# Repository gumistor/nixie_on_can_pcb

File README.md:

# nixie_on_can_pcb
Six NIXIE display with CAN bus interface. Powered with step up regulator.

Main controler: PIC18F2480
CAN transciever: MCP2551

PIC utylize PWM output to drive step-up regulator. 
Step-up regulator provides high voltage to lamps (over 100V!!). 
PIC uses multiplexing to light up digits.

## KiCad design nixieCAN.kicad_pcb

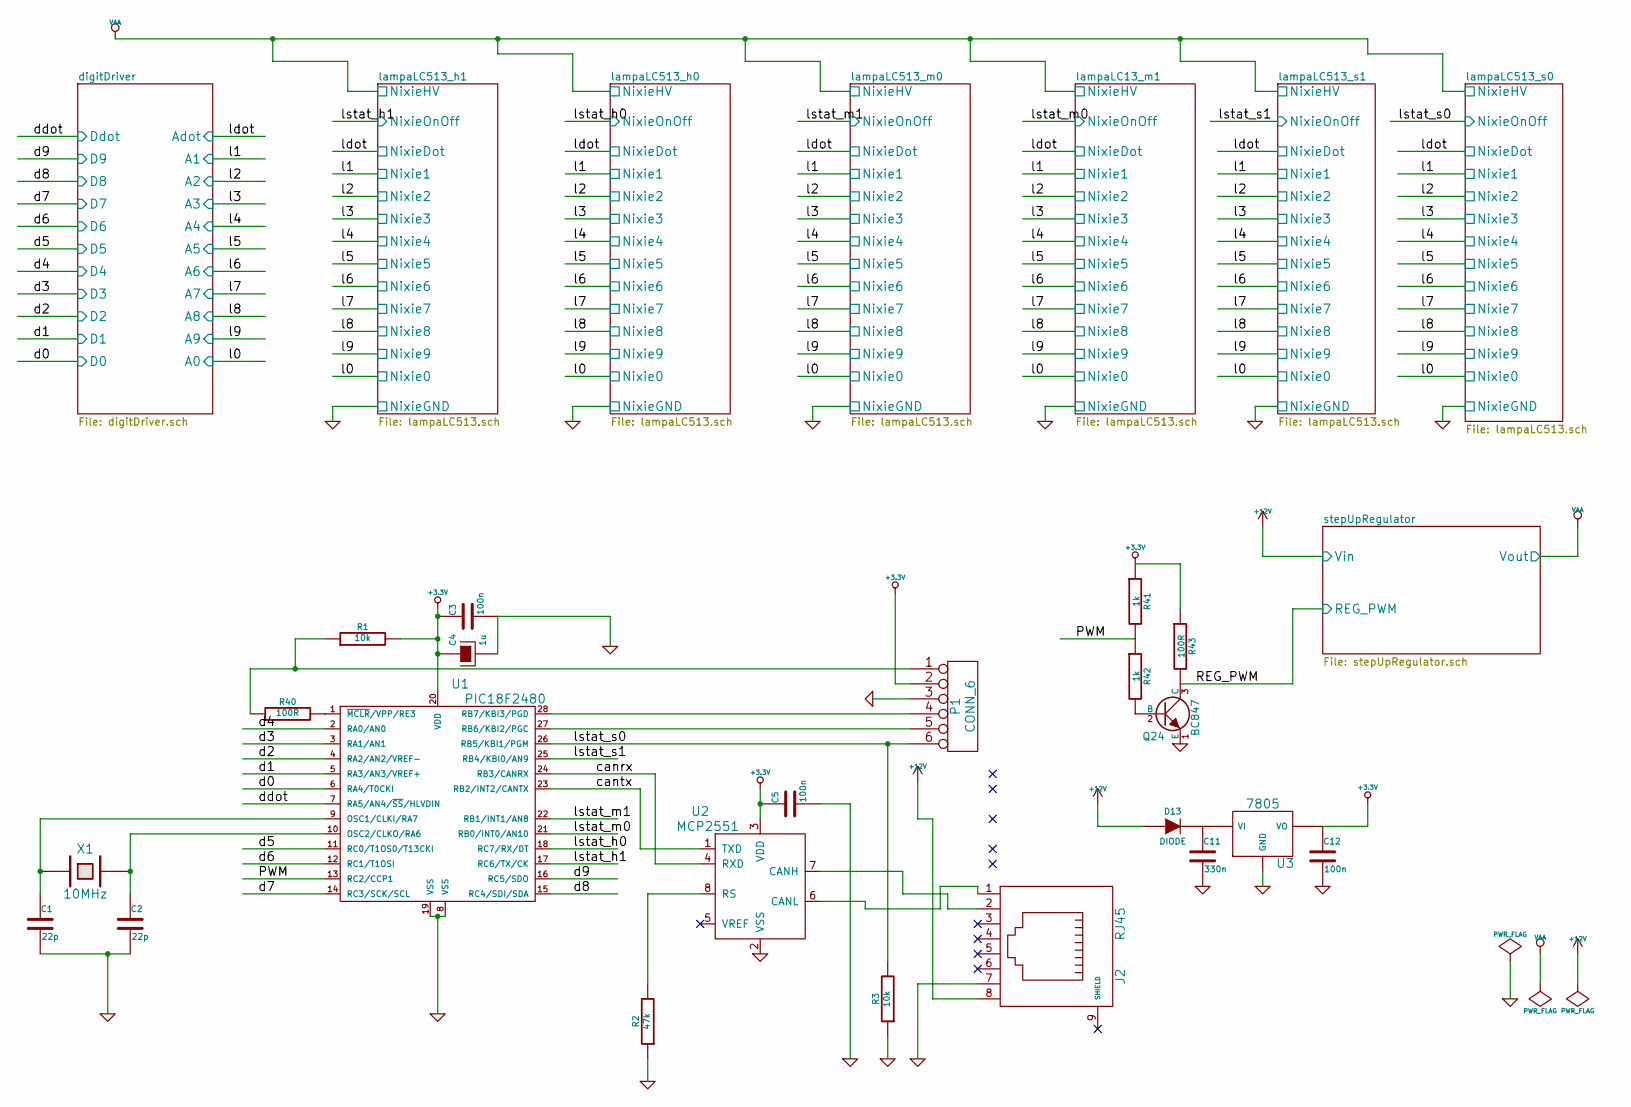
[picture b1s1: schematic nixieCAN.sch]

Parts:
C1, C2: 22p
C3, C5, C12: 100n
C4: 1u
C11: 330n
D13: DIODE
J2: RJ45
P1: CONN_6
Q24: BC847
R1, R3: 10k
R2: 47k
R40, R43: 100R
R41, R42: 1k
U1: PIC18F2480
U2: MCP2551
U3: 7805
X1: 10MHz

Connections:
+3.3V: C3.1, C4.1, C5.1, C12.1, P1.2, R1.2, R41.1, R43.1, U1.20 (VDD), U2.3 (VDD), U3.3 (VO)
+12V: D13.1 (A), J2.8; also elsewhere on the board
/PWM: R41.2, R42.1, U1.13 (RC2/CCP1)
/canrx: U1.24 (RB3/CANRX), U2.4 (RXD)
/cantx: U1.23 (RB2/INT2/CANTX), U2.1 (TXD)
/digitDriver/D0: U1.6 (RA4/T0CKI); also elsewhere on the board
/digitDriver/D1: U1.5 (RA3/AN3/VREF+); also elsewhere on the board
/digitDriver/D2: U1.4 (RA2/AN2/VREF-); also elsewhere on the board
/digitDriver/D3: U1.3 (RA1/AN1); also elsewhere on the board
/digitDriver/D4: U1.2 (RA0/AN0); also elsewhere on the board
/digitDriver/D5: U1.11 (RC0/T1OS0/T13CKI); also elsewhere on the board
/digitDriver/D6: U1.12 (RC1/T1OSI); also elsewhere on the board
/digitDriver/D7: U1.14 (RC3/SCK/SCL); also elsewhere on the board
/digitDriver/D8: U1.15 (RC4/SDI/SDA); also elsewhere on the board
/digitDriver/D9: U1.16 (RC5/SDO); also elsewhere on the board
/digitDriver/Ddot: U1.7 (RA5/AN4/~SS~/HLVDIN); also elsewhere on the board
/lampaLC13_m1/NixieOnOff: U1.21 (RB0/INT0/AN10); also elsewhere on the board
/lampaLC513_h0/NixieOnOff: U1.18 (RC7/RX/DT); also elsewhere on the board
/lampaLC513_h1/NixieOnOff: U1.17 (RC6/TX/CK); also elsewhere on the board
/lampaLC513_m0/NixieOnOff: U1.22 (RB1/INT1/AN8); also elsewhere on the board
/lampaLC513_s0/NixieOnOff: P1.6, R3.2, U1.26 (RB5/KBI1/PGM); also elsewhere on the board
/lampaLC513_s1/NixieOnOff: U1.25 (RB4/KBI0/AN9); also elsewhere on the board
/stepUpRegulator/REG_PWM: Q24.3 (C), R43.2; also elsewhere on the board
GND: C1.2, C2.2, C3.2, C4.2, C5.2, C11.2, C12.2, J2.7, P1.3, Q24.1 (E), R2.1, R3.1, U1.8 (VSS), U1.19 (VSS), U2.2 (VSS), U3.2 (GND); also elsewhere on the board
unnamed: P1.5, U1.27 (RB6/KBI2/PGC)
unnamed: R2.2, U2.8 (RS)
unnamed: J2.1, U2.6 (CANL)
unnamed: C11.1, D13.2 (K), U3.1 (VI)
unnamed: J2.2, U2.7 (CANH)
unnamed: Q24.2 (B), R42.2
unnamed: P1.4, U1.28 (RB7/KBI3/PGD)
unnamed: P1.1, R1.1, R40.1
unnamed: R40.2, U1.1 (~MCLR~/VPP/RE3)
unnamed: C1.1, U1.9 (OSC1/CLKI/RA7), X1.1
unnamed: C2.1, U1.10 (OSC2/CLKO/RA6), X1.2

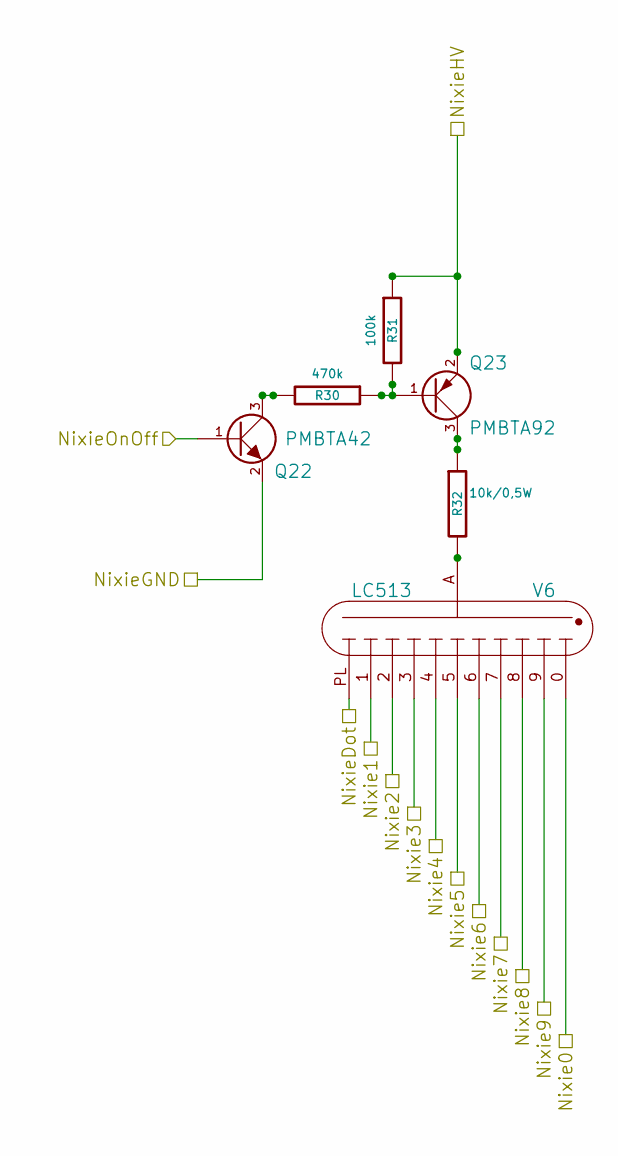
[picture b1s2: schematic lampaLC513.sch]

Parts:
Q1: PMBTA42; SOT23
Q2: PMBTA92; SOT23
R4: 470k
R5: 100k
R6: 10k/0,5W
V1: LC513

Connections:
/digitDriver/A0: V1.0; also elsewhere on the board
/digitDriver/A1: V1.1; also elsewhere on the board
/digitDriver/A2: V1.2; also elsewhere on the board
/digitDriver/A3: V1.3; also elsewhere on the board
/digitDriver/A4: V1.4; also elsewhere on the board
/digitDriver/A5: V1.5; also elsewhere on the board
/digitDriver/A6: V1.6; also elsewhere on the board
/digitDriver/A7: V1.7; also elsewhere on the board
/digitDriver/A8: V1.8; also elsewhere on the board
/digitDriver/A9: V1.9; also elsewhere on the board
/digitDriver/Adot: V1.PL; also elsewhere on the board
/lampaLC513_s0/NixieOnOff: Q1.1 (B); also elsewhere on the board
GND: Q1.2 (E); also elsewhere on the board
unnamed: R6.2, V1.A
unnamed: Q2.3 (C), R6.1
unnamed: Q2.1 (B), R4.1, R5.2
unnamed: Q1.3 (C), R4.2
VAA: Q2.2 (E), R5.1; also elsewhere on the board

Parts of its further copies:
Q3, Q16, Q18, Q20, Q22: PMBTA42; SOT23
Q4, Q17, Q19, Q21, Q23: PMBTA92; SOT23
R7, R21, R24, R27, R30: 470k
R8, R22, R25, R28, R31: 100k
R9, R23, R26, R29, R32: 10k/0,5W
V2, V3, V4, V5, V6: LC513

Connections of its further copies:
/digitDriver/A0: V2.0, V3.0, V4.0, V5.0, V6.0; also elsewhere on the board
/digitDriver/A1: V2.1, V3.1, V4.1, V5.1, V6.1; also elsewhere on the board
/digitDriver/A2: V2.2, V3.2, V4.2, V5.2, V6.2; also elsewhere on the board
/digitDriver/A3: V2.3, V3.3, V4.3, V5.3, V6.3; also elsewhere on the board
/digitDriver/A4: V2.4, V3.4, V4.4, V5.4, V6.4; also elsewhere on the board
/digitDriver/A5: V2.5, V3.5, V4.5, V5.5, V6.5; also elsewhere on the board
/digitDriver/A6: V2.6, V3.6, V4.6, V5.6, V6.6; also elsewhere on the board
/digitDriver/A7: V2.7, V3.7, V4.7, V5.7, V6.7; also elsewhere on the board
/digitDriver/A8: V2.8, V3.8, V4.8, V5.8, V6.8; also elsewhere on the board
/digitDriver/A9: V2.9, V3.9, V4.9, V5.9, V6.9; also elsewhere on the board
/digitDriver/Adot: V2.PL, V3.PL, V4.PL, V5.PL, V6.PL; also elsewhere on the board
/lampaLC13_m1/NixieOnOff: Q18.1 (B); also elsewhere on the board
/lampaLC513_h0/NixieOnOff: Q20.1 (B); also elsewhere on the board
/lampaLC513_h1/NixieOnOff: Q22.1 (B); also elsewhere on the board
/lampaLC513_m0/NixieOnOff: Q16.1 (B); also elsewhere on the board
/lampaLC513_s1/NixieOnOff: Q3.1 (B); also elsewhere on the board
GND: Q3.2 (E), Q16.2 (E), Q18.2 (E), Q20.2 (E), Q22.2 (E); also elsewhere on the board
unnamed: R9.2, V2.A
unnamed: Q4.1 (B), R7.1, R8.2
unnamed: Q4.3 (C), R9.1
unnamed: Q3.3 (C), R7.2
unnamed: R23.2, V3.A
unnamed: Q17.3 (C), R23.1
unnamed: Q17.1 (B), R21.1, R22.2
unnamed: Q16.3 (C), R21.2
unnamed: Q19.1 (B), R24.1, R25.2
unnamed: Q18.3 (C), R24.2
unnamed: R26.2, V4.A
unnamed: Q19.3 (C), R26.1
unnamed: Q20.3 (C), R27.2
unnamed: Q21.1 (B), R27.1, R28.2
unnamed: R29.2, V5.A
unnamed: Q21.3 (C), R29.1
unnamed: Q22.3 (C), R30.2
unnamed: Q23.1 (B), R30.1, R31.2
unnamed: R32.2, V6.A
unnamed: Q23.3 (C), R32.1
VAA: Q4.2 (E), Q17.2 (E), Q19.2 (E), Q21.2 (E), Q23.2 (E), R8.1, R22.1, R25.1, R28.1, R31.1; also elsewhere on the board

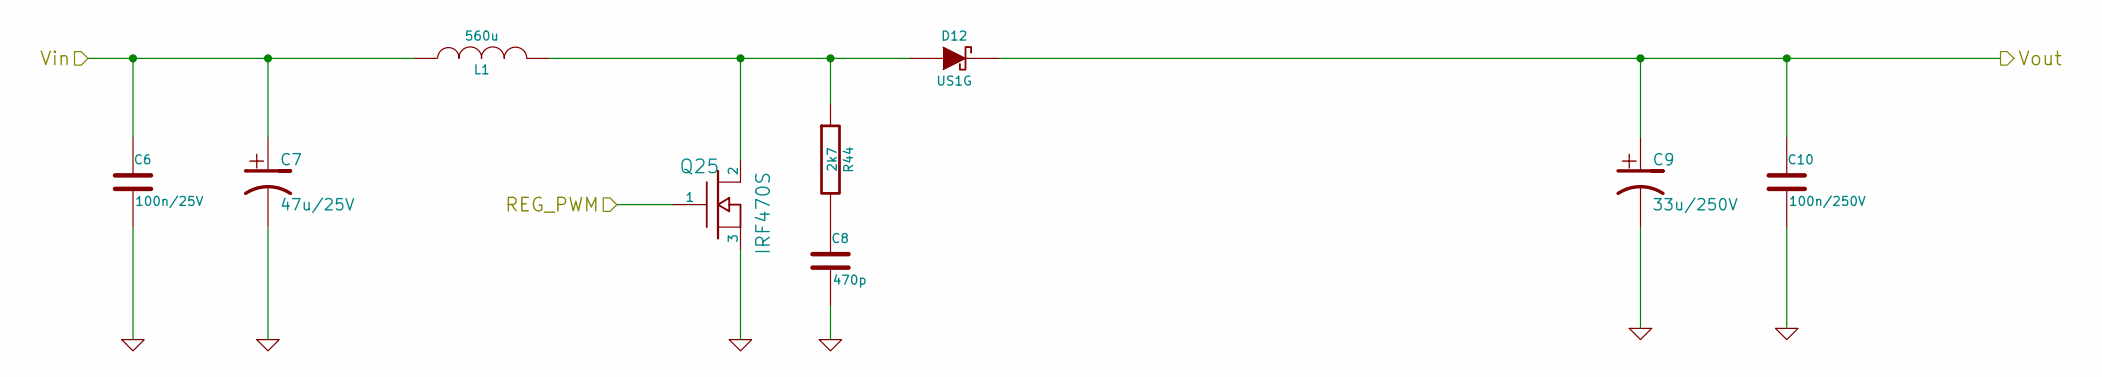
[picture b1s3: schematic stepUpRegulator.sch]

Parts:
C6: 100n/25V
C7: 47u/25V
C8: 470p
C9: 33u/250V
C10: 100n/250V
D12: US1G
L1: 560u
Q25: IRF470S
R44: 2k7

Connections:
+12V: C6.1, C7.1, L1.1; also elsewhere on the board
/stepUpRegulator/REG_PWM: Q25.1; also elsewhere on the board
GND: C6.2, C7.2, C8.2, C9.2, C10.2, Q25.3; also elsewhere on the board
unnamed: C8.1, R44.2
unnamed: D12.1 (A), L1.2, Q25.2, R44.1
VAA: C9.1, C10.1, D12.2 (K); also elsewhere on the board

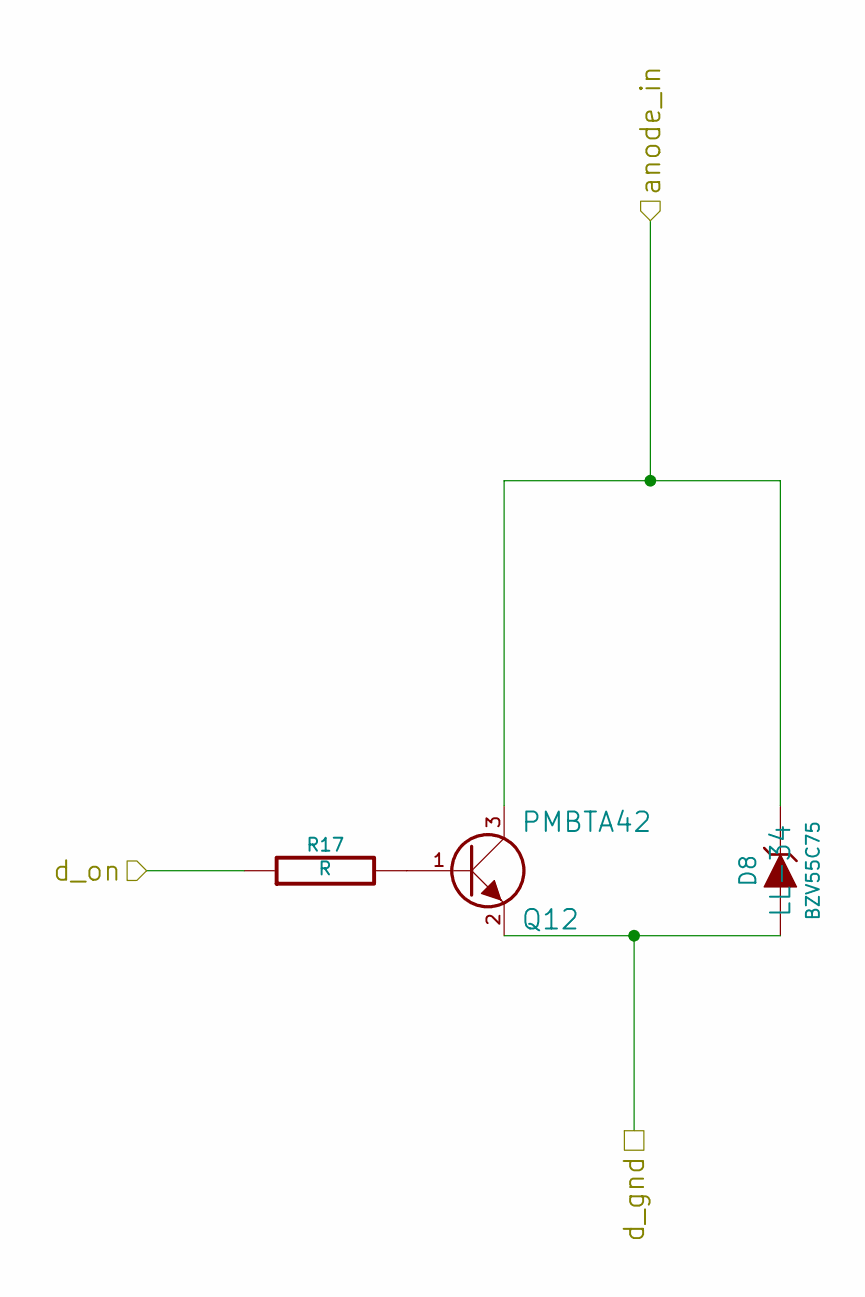
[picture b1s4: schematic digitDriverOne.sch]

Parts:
D1: BZV55C75; LL-34
Q5: PMBTA42; SOT23
R10: R

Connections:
/digitDriver/Adot: D1.2 (K), Q5.3 (C); also elsewhere on the board
/digitDriver/Ddot: R10.1; also elsewhere on the board
GND: D1.1 (A), Q5.2 (E); also elsewhere on the board
unnamed: Q5.1 (B), R10.2

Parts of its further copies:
D2, D3, D4, D5, D6, D7, D8, D9, D10, D11: BZV55C75; LL-34
Q6, Q7, Q8, Q9, Q10, Q11, Q12, Q13, Q14, Q15: PMBTA42; SOT23
R11, R12, R13, R14, R15, R16, R17, R18, R19, R20: R

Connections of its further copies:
/digitDriver/A0: D11.2 (K), Q15.3 (C); also elsewhere on the board
/digitDriver/A1: D2.2 (K), Q6.3 (C); also elsewhere on the board
/digitDriver/A2: D3.2 (K), Q7.3 (C); also elsewhere on the board
/digitDriver/A3: D4.2 (K), Q8.3 (C); also elsewhere on the board
/digitDriver/A4: D5.2 (K), Q9.3 (C); also elsewhere on the board
/digitDriver/A5: D6.2 (K), Q10.3 (C); also elsewhere on the board
/digitDriver/A6: D7.2 (K), Q11.3 (C); also elsewhere on the board
/digitDriver/A7: D8.2 (K), Q12.3 (C); also elsewhere on the board
/digitDriver/A8: D9.2 (K), Q13.3 (C); also elsewhere on the board
/digitDriver/A9: D10.2 (K), Q14.3 (C); also elsewhere on the board
/digitDriver/D0: R20.1; also elsewhere on the board
/digitDriver/D1: R19.1; also elsewhere on the board
/digitDriver/D2: R18.1; also elsewhere on the board
/digitDriver/D3: R17.1; also elsewhere on the board
/digitDriver/D4: R16.1; also elsewhere on the board
/digitDriver/D5: R15.1; also elsewhere on the board
/digitDriver/D6: R14.1; also elsewhere on the board
/digitDriver/D7: R13.1; also elsewhere on the board
/digitDriver/D8: R12.1; also elsewhere on the board
/digitDriver/D9: R11.1; also elsewhere on the board
GND: D2.1 (A), D3.1 (A), D4.1 (A), D5.1 (A), D6.1 (A), D7.1 (A), D8.1 (A), D9.1 (A), D10.1 (A), D11.1 (A), Q6.2 (E), Q7.2 (E), Q8.2 (E), Q9.2 (E), Q10.2 (E), Q11.2 (E), Q12.2 (E), Q13.2 (E), Q14.2 (E), Q15.2 (E); also elsewhere on the board
unnamed: Q6.1 (B), R11.2
unnamed: Q7.1 (B), R12.2
unnamed: Q8.1 (B), R13.2
unnamed: Q9.1 (B), R14.2
unnamed: Q10.1 (B), R15.2
unnamed: Q11.1 (B), R16.2
unnamed: Q12.1 (B), R17.2
unnamed: Q13.1 (B), R18.2
unnamed: Q14.1 (B), R19.2
unnamed: Q15.1 (B), R20.2

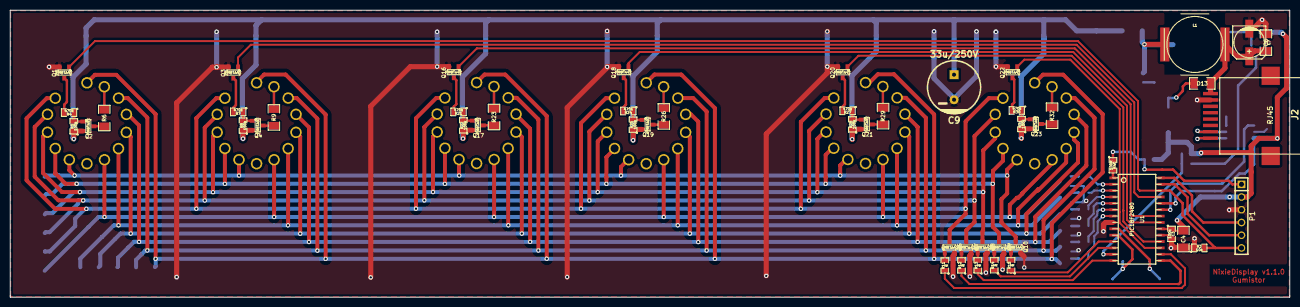
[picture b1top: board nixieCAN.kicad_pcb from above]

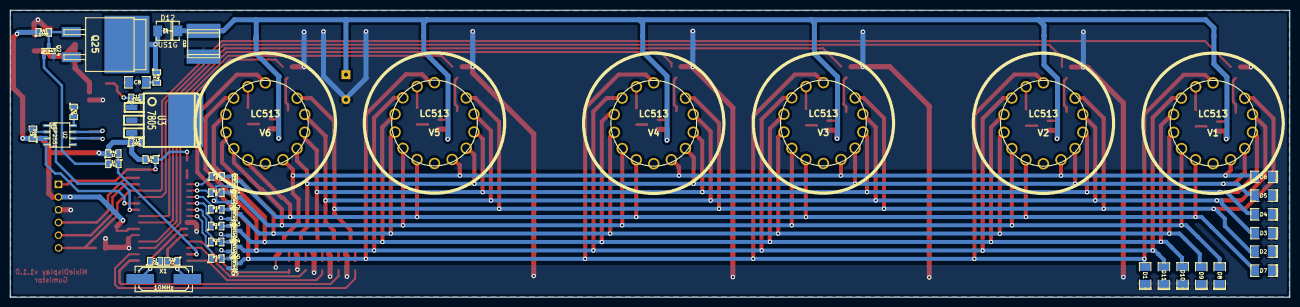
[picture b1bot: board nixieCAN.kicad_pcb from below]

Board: 2 copper layers, 255.3 x 57.2 mm, 100 parts (48 on the bottom side), 84 nets.

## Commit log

2021-11-25 Initial version.
